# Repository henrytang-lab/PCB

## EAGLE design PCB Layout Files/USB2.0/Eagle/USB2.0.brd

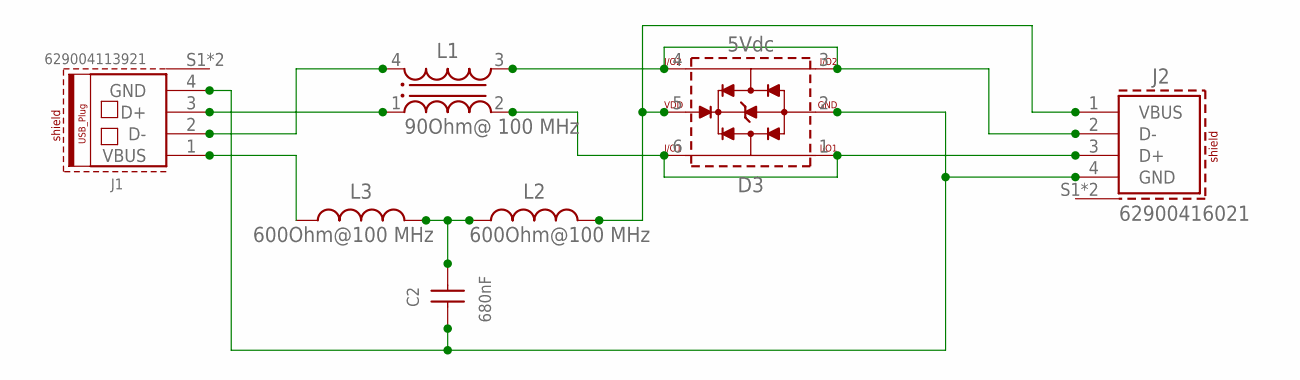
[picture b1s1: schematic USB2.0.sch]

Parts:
C2: 680nF; WCAP-CSGP_0603_R
D3: 5Vdc; WE-TVS_SOT23-6L
J1: 629004113921
J2: 62900416021
L1: 90Ohm@ 100 MHz; WE-CNSW_1206
L2, L3: 600Ohm@100 MHz; WE-CBF_0603(W=2.6)

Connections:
DX_N: J1.2 (D-), L1.4 (1)
DX_P: J1.3 (D+), L1.1 (4)
D_N: D3.3 (I/O2), D3.4 (I/O4), J2.2 (D-), L1.3 (2)
D_P: D3.1 (I/O1), D3.6 (I/O3), J2.3 (D+), L1.2 (3)
unnamed: D3.5 (VDD), J2.1 (VBUS), L2.2
unnamed: C2.1, D3.2 (GND), J1.4 (GND), J2.4 (GND)
unnamed: J1.1 (VBUS), L3.1
unnamed: C2.2, L2.1, L3.2

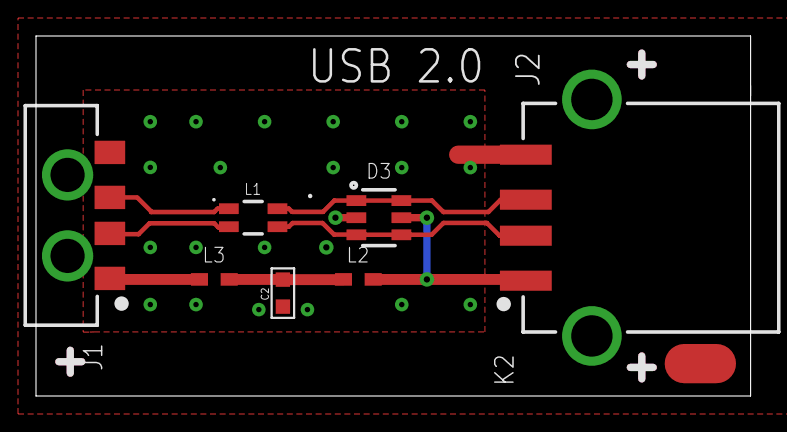
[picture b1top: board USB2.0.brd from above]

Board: 8 copper layers, 39.7 x 20.0 mm, 7 parts (0 on the bottom side), 8 nets.

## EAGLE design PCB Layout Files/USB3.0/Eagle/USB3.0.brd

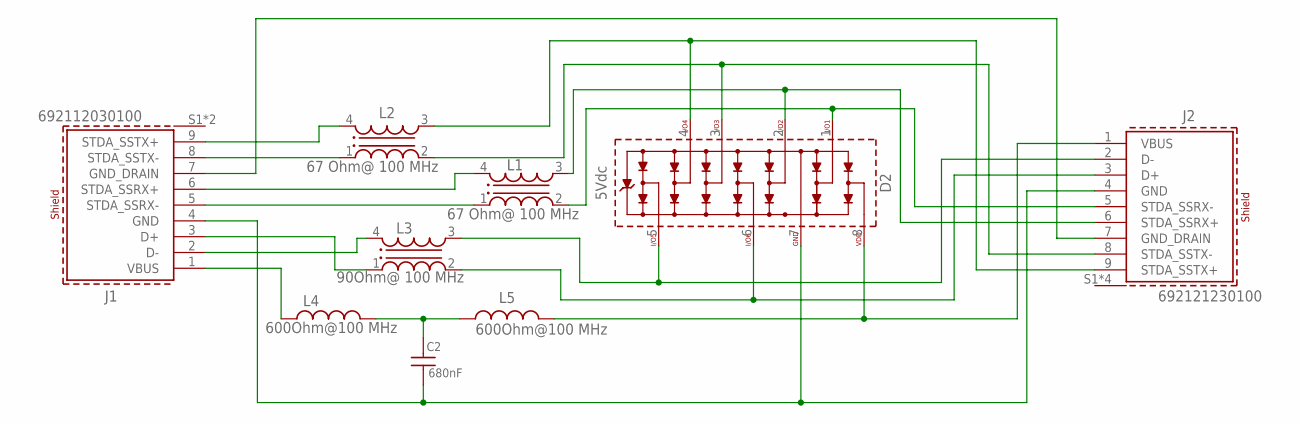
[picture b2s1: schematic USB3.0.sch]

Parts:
C2: 680nF; WCAP-CSGP_0603_W
D2: 5Vdc; WE-TVS_MSOP-8L
J1: 692112030100
J2: 692121230100
L1, L2: 67 Ohm@ 100 MHz; WE-CNSW_HF_0805
L3: 90Ohm@ 100 MHz; WE-CNSW_1206
L4, L5: 600Ohm@100 MHz; WE-CBF_0805(W=4.0)

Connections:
DX_N: J1.2 (D-), L3.4 (1)
DX_P: J1.3 (D+), L3.1 (4)
D_N: D2.5 (I/O5), J2.2 (D-), L3.3 (2)
D_P: D2.6 (I/O6), J2.3 (D+), L3.2 (3)
unnamed: D2.8 (VDD), J2.1 (VBUS), L5.2
unnamed: J1.7 (GND_DRAIN), J2.7 (GND_DRAIN)
unnamed: C2.1, D2.7 (GND), J1.4 (GND), J2.4 (GND)
unnamed: C2.2, L4.2, L5.1
unnamed: J1.1 (VBUS), L4.1
RX_N: J1.5 (STDA_SSRX-), L1.1 (4)
RX_P: J1.6 (STDA_SSRX+), L1.4 (1)
R_N: D2.1 (I/O1), J2.5 (STDA_SSRX-), L1.2 (3)
R_P: D2.2 (I/O2), J2.6 (STDA_SSRX+), L1.3 (2)
TX_N: J1.8 (STDA_SSTX-), L2.1 (4)
TX_P: J1.9 (STDA_SSTX+), L2.4 (1)
T_N: D2.3 (I/O3), J2.8 (STDA_SSTX-), L2.2 (3)
T_P: D2.4 (I/O4), J2.9 (STDA_SSTX+), L2.3 (2)

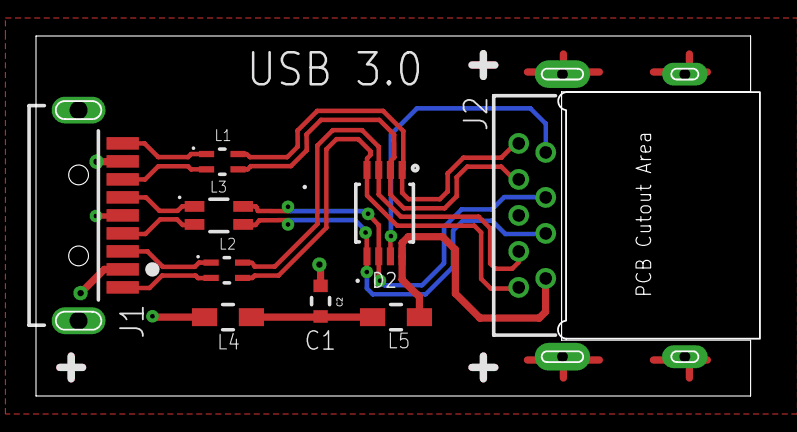
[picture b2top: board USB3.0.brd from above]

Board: 8 copper layers, 40.2 x 20.0 mm, 9 parts (0 on the bottom side), 17 nets.

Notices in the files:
parts and their libraries:
Wurth_Connectors_WR-USB: Copyright: Würth Elektronik
